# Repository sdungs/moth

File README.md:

# MoTH
Monitoring Of Temperature and Humidity using Arduino. Including designs for Arduino shields, firmware and python readout scripts.

## MoTH-8
MoTH-8 is an Arduinio shield which is forseen to readout 8 NTCs/PTCs and 8 enviromental sensors. It also provides a connection for a LCD screen and WIFI module.

Sensor connection:

### BOM
- Board-To-Board Connector, 2.54mm, header (shield to Arduino connection)
- 2 contacts pin header (Molex): 22-27-2021
- 3 contacts pin header (Molex): 22-27-2031
- 4 contacts pin header (Molex): 22-27-2041
- SMD resistors foot print: 1206
- WIFI module: ESP8266 ESP-01

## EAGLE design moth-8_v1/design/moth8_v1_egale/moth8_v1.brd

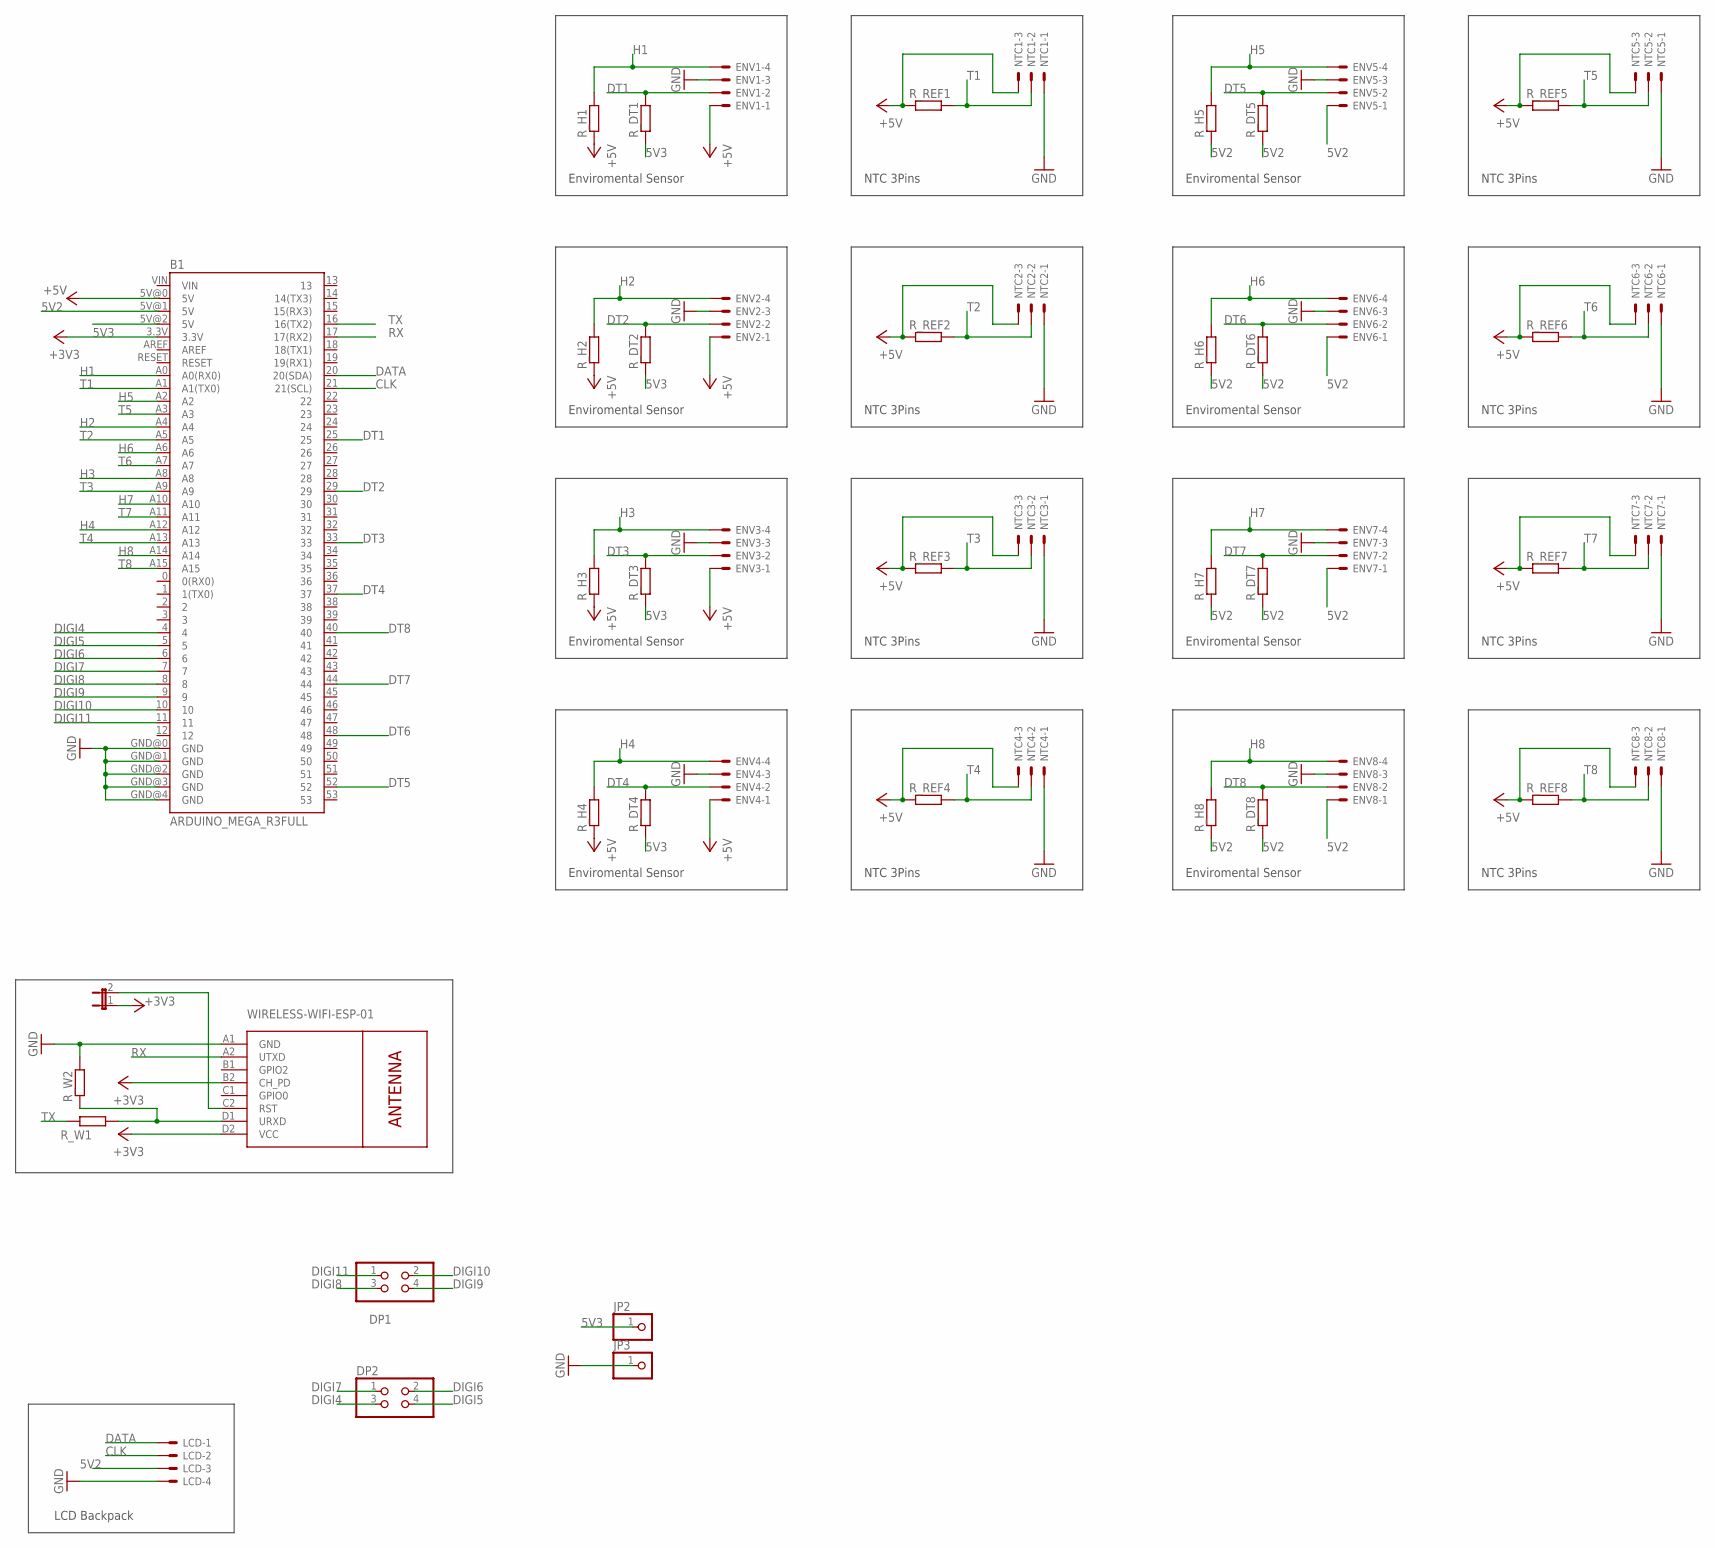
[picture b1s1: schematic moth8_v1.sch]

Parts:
B1: ARDUINO_MEGA_R3FULL; ARDUINO_MEGA
DP1, DP2: PINHD-2X2; 2X02
ENV1, ENV2, ENV3, ENV4, ENV5, ENV6, ENV7, ENV8: 22-27-2041-04; 6410-04
ESP-01: WIRELESS-WIFI-ESP-01
JP1: JP1E; JP1
JP2, JP3: PINHD-1X1; 1X01
LCD: 22-27-2041-04; 6410-04
NTC1, NTC2, NTC3, NTC4, NTC5, NTC6, NTC7, NTC8: 22-27-2031-03; 6410-03
R_DT1, R_DT2, R_DT3, R_DT4, R_DT5, R_DT6, R_DT7, R_DT8: R-EU_R1206; R1206
R_H1, R_H2, R_H3, R_H4, R_H5, R_H6, R_H7, R_H8: R-EU_R1206; R1206
R_REF1, R_REF2, R_REF3, R_REF4, R_REF5, R_REF6, R_REF7, R_REF8: R-EU_R1206; R1206
R_W1, R_W2: R-EU_R1206; R1206

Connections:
5V2: B1.5V@1 (5V), ENV5.1, ENV6.1, ENV7.1, ENV8.1, LCD.3, R_DT5.1, R_DT6.1, R_DT7.1, R_DT8.1, R_H5.1, R_H6.1, R_H7.1, R_H8.1
5V3: B1.5V@2 (5V), JP2.1, R_DT1.1, R_DT2.1, R_DT3.1, R_DT4.1
+3V3: B1.3.3V, ESP-01.B2 (CH_PD), ESP-01.D2 (VCC), JP1.1
+5V: B1.5V@0 (5V), ENV1.1, ENV2.1, ENV3.1, ENV4.1, NTC1.3, NTC2.3, NTC3.3, NTC4.3, NTC5.3, NTC6.3, NTC7.3, NTC8.3, R_H1.1, R_H2.1, R_H3.1, R_H4.1, R_REF1.1, R_REF2.1, R_REF3.1, R_REF4.1, R_REF5.1, R_REF6.1, R_REF7.1, R_REF8.1
CLK: B1.21 (21(SCL)), LCD.2
DATA: B1.20 (20(SDA)), LCD.1
DIGI4: B1.4, DP2.3
DIGI5: B1.5, DP2.4
DIGI6: B1.6, DP2.2
DIGI7: B1.7, DP2.1
DIGI8: B1.8, DP1.3
DIGI9: B1.9, DP1.4
DIGI10: B1.10, DP1.2
DIGI11: B1.11, DP1.1
DT1: B1.25, ENV1.2, R_DT1.2
DT2: B1.29, ENV2.2, R_DT2.2
DT3: B1.33, ENV3.2, R_DT3.2
DT4: B1.37, ENV4.2, R_DT4.2
DT5: B1.52, ENV5.2, R_DT5.2
DT6: B1.48, ENV6.2, R_DT6.2
DT7: B1.44, ENV7.2, R_DT7.2
DT8: B1.40, ENV8.2, R_DT8.2
GND: B1.GND@0 (GND), B1.GND@1 (GND), B1.GND@2 (GND), B1.GND@3 (GND), B1.GND@4 (GND), ENV1.3, ENV2.3, ENV3.3, ENV4.3, ENV5.3, ENV6.3, ENV7.3, ENV8.3, ESP-01.A1 (GND), JP3.1, LCD.4, NTC1.1, NTC2.1, NTC3.1, NTC4.1, NTC5.1, NTC6.1, NTC7.1, NTC8.1, R_W2.2
H1: B1.A0 (A0(RX0)), ENV1.4, R_H1.2
H2: B1.A4, ENV2.4, R_H2.2
H3: B1.A8, ENV3.4, R_H3.2
H4: B1.A12, ENV4.4, R_H4.2
H5: B1.A2, ENV5.4, R_H5.2
H6: B1.A6, ENV6.4, R_H6.2
H7: B1.A10, ENV7.4, R_H7.2
H8: B1.A14, ENV8.4, R_H8.2
unnamed: ESP-01.D1 (URXD), R_W1.2, R_W2.1
unnamed: ESP-01.C2 (RST), JP1.2
RX: B1.17 (17(RX2)), ESP-01.A2 (UTXD)
T1: B1.A1 (A1(TX0)), NTC1.2, R_REF1.2
T2: B1.A5, NTC2.2, R_REF2.2
T3: B1.A9, NTC3.2, R_REF3.2
T4: B1.A13, NTC4.2, R_REF4.2
T5: B1.A3, NTC5.2, R_REF5.2
T6: B1.A7, NTC6.2, R_REF6.2
T7: B1.A11, NTC7.2, R_REF7.2
T8: B1.A15, NTC8.2, R_REF8.2
TX: B1.16 (16(TX2)), R_W1.1

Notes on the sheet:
Enviromental Sensor
NTC 3Pins
LCD Backpack

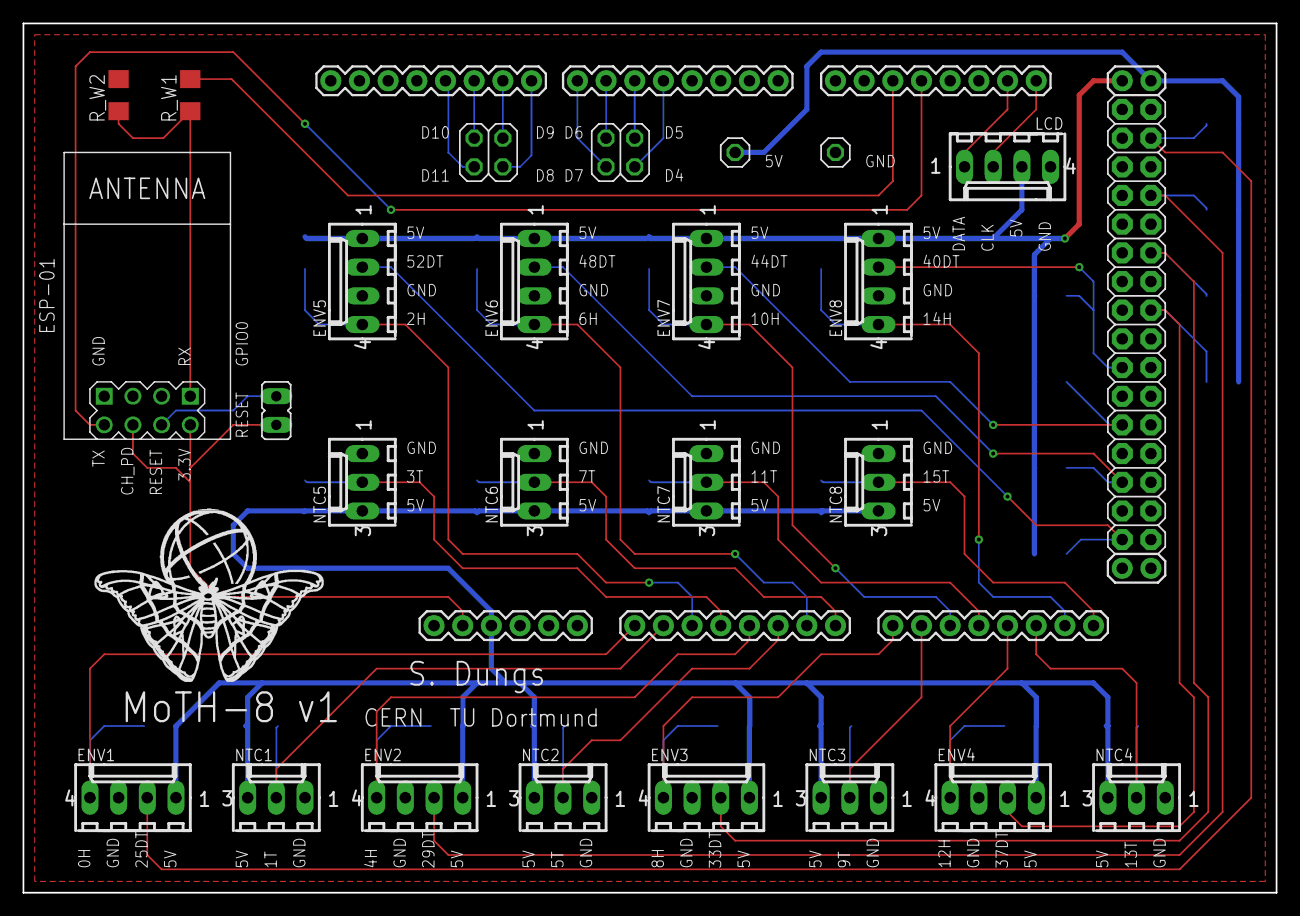
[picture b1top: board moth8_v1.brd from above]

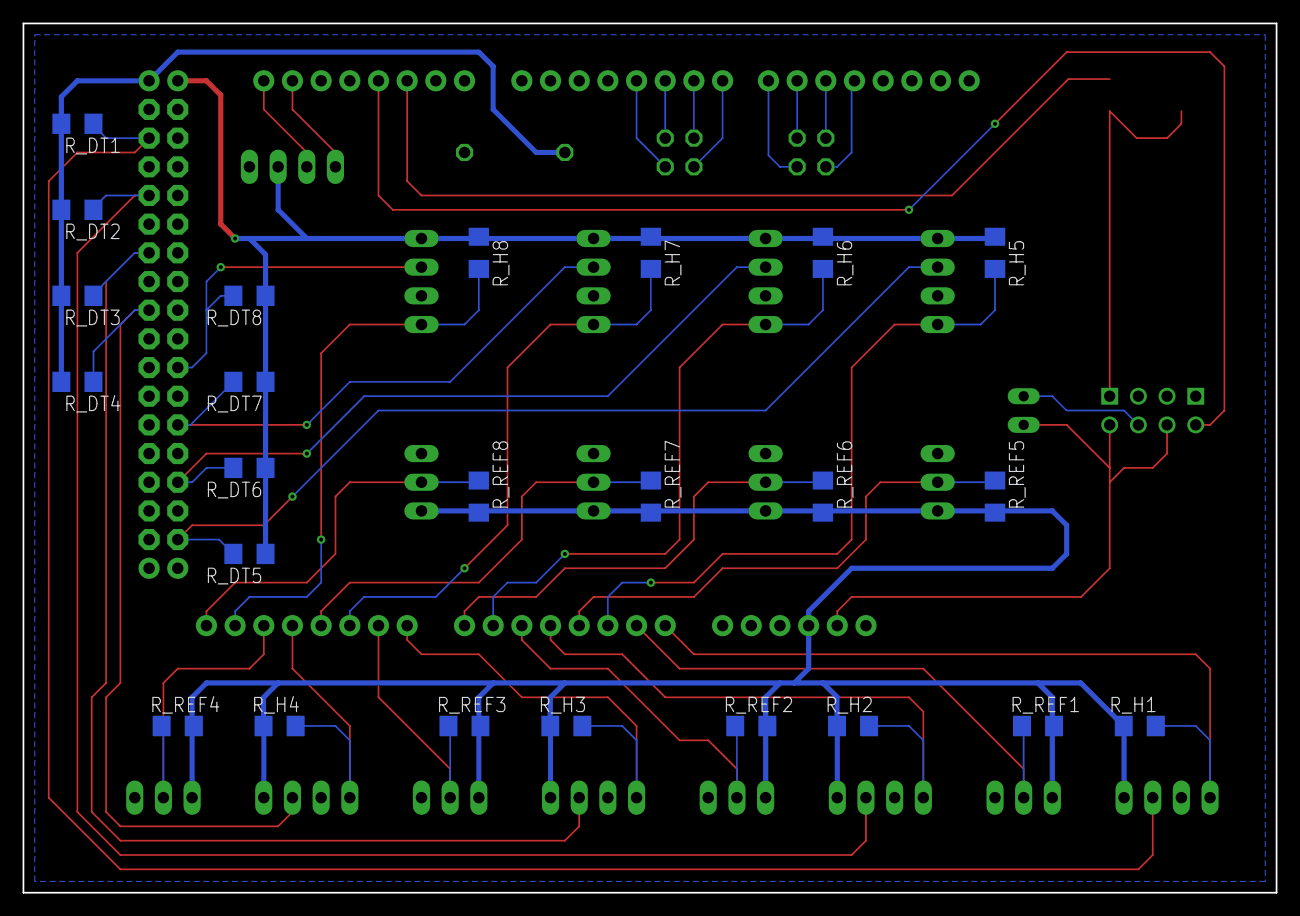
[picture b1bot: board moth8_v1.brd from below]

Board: 2 copper layers, 111.0 x 77.0 mm, 50 parts (24 on the bottom side), 43 nets.

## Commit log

2019-11-05 moth-8_v1
2019-11-05 readme init
2019-11-05 moth-8_v1 pngs
2019-11-05 typo
2019-11-06 sensor connections
2020-05-25 bomv1

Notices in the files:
parts and their libraries:
Arduino_Mega_Shield_v1: Licensing: Creative Commons ShareAlike 4.0 International - https://creativecommons.org/licenses/by-sa/4.0
diy-modules: Released under the Creative Commons Attribution 4.0 International License: http://creativecommons.org/licenses/by/4.0
